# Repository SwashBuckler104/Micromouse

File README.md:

# Micromouse
80 x 80 mm Micromouse,

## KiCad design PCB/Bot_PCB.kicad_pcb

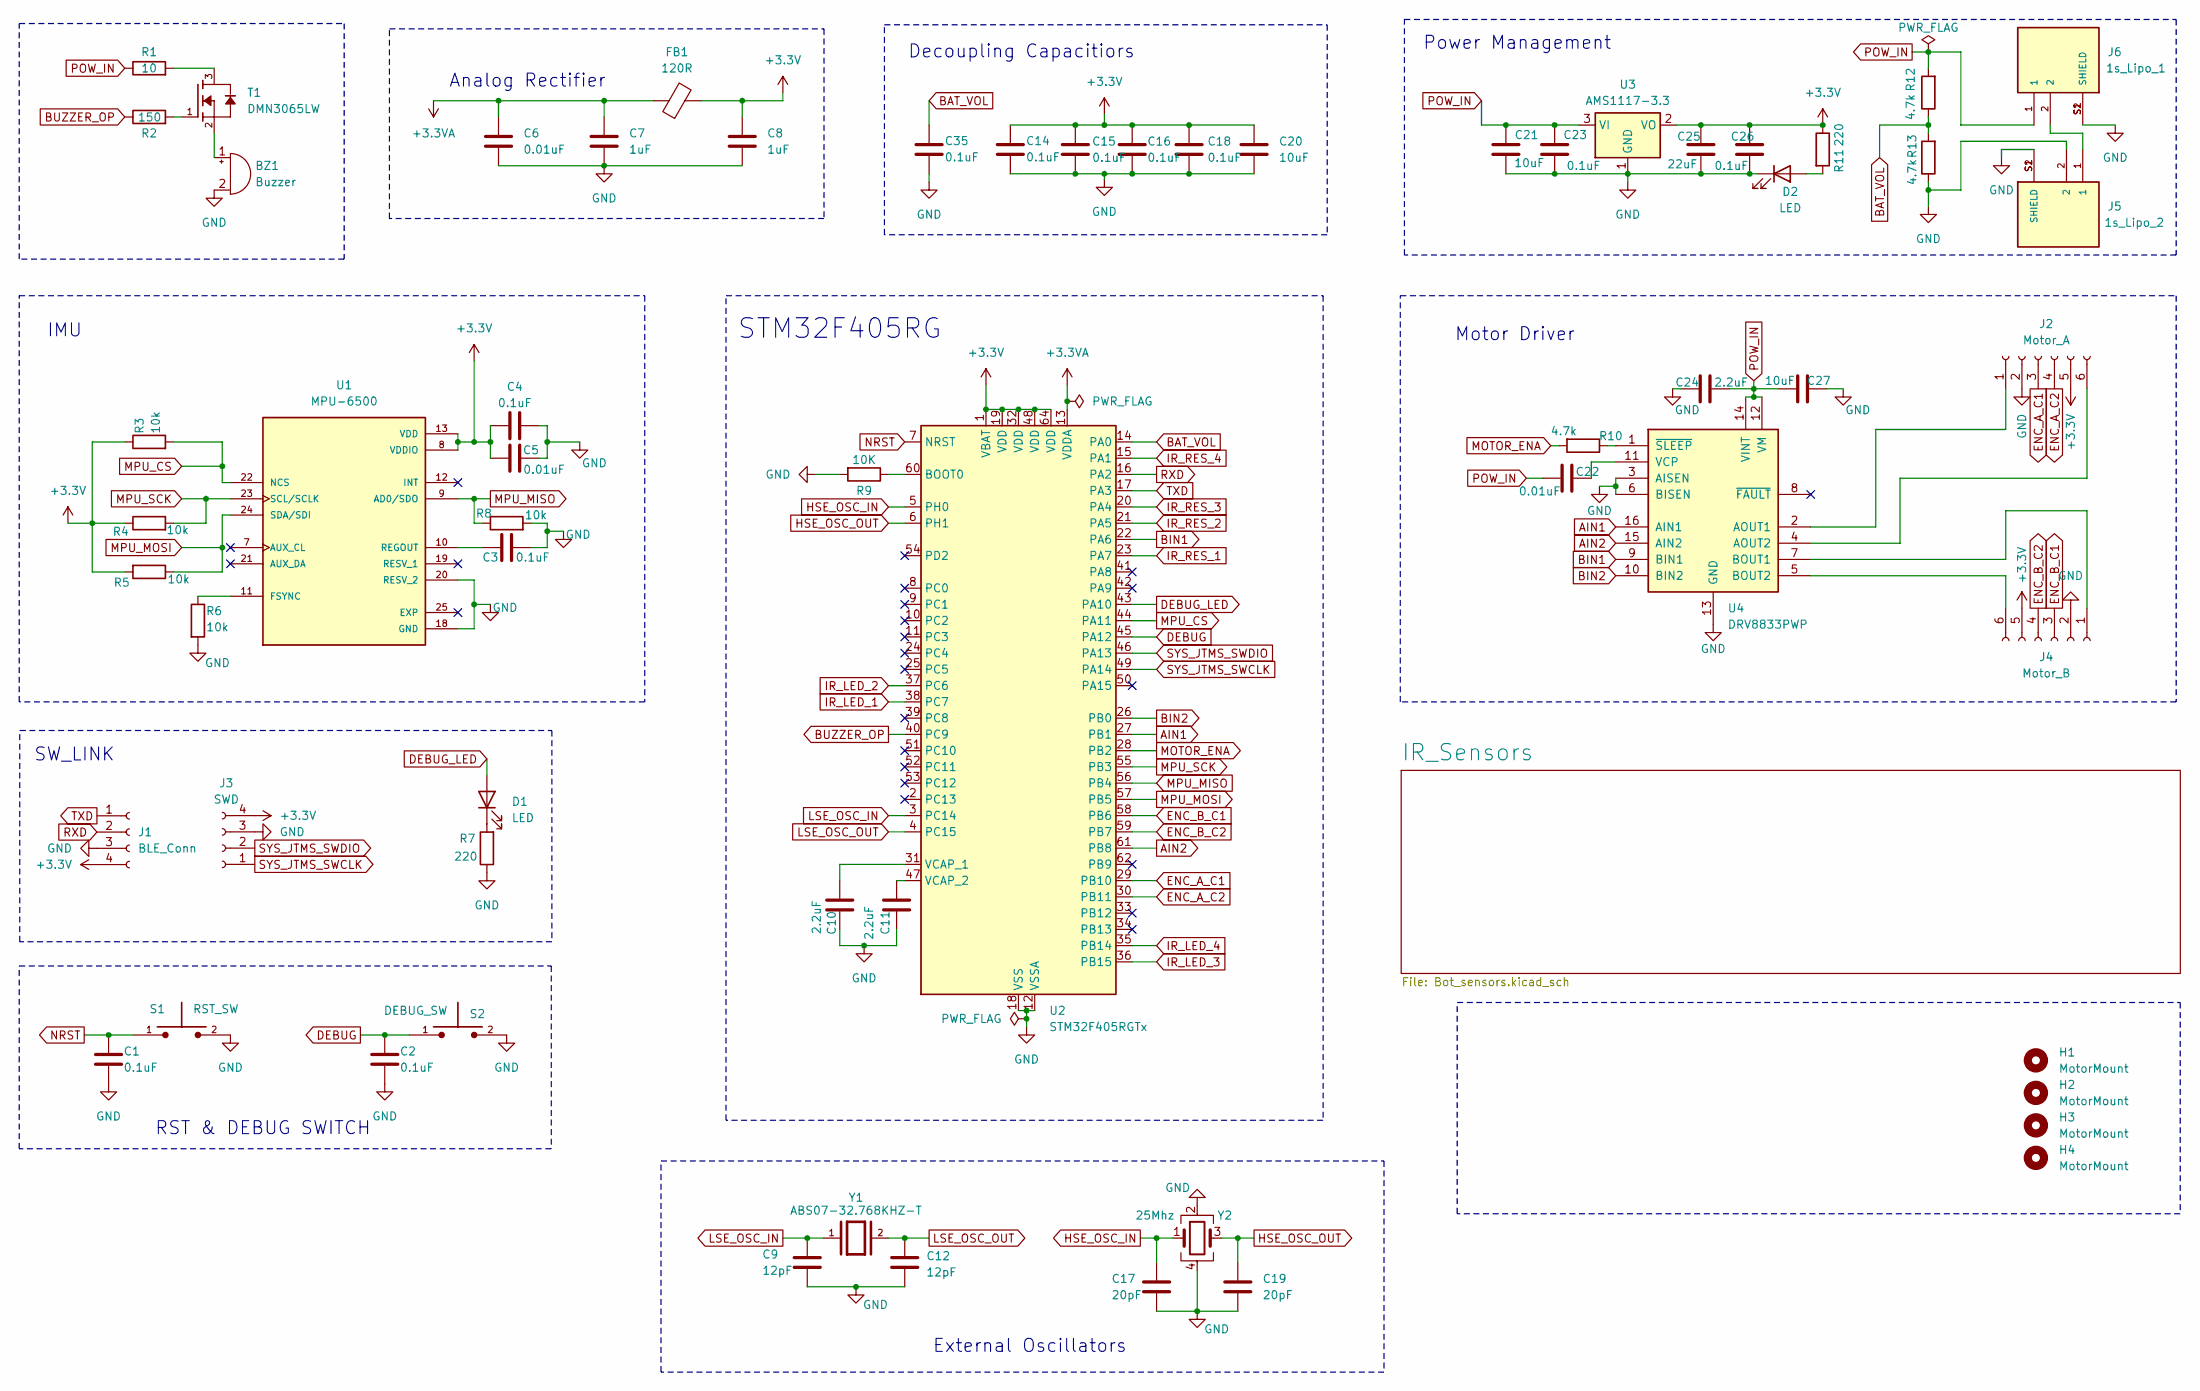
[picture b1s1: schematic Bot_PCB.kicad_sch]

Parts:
BZ1: Buzzer; Buzzer_Murata_PKMCS0909E
C1, C2, C3, C4, C14, C15, C16, C18, C23, C26, C35: 0.1uF; C_0402_1005Metric_Pad0.74x0.62mm_HandSolder
C5, C6, C22: 0.01uF; C_0402_1005Metric_Pad0.74x0.62mm_HandSolder
C7, C8: 1uF; C_0603_1608Metric_Pad1.08x0.95mm_HandSolder
C9, C12: 12pF; C_0402_1005Metric_Pad0.74x0.62mm_HandSolder
C10, C11, C24: 2.2uF; C_0603_1608Metric_Pad1.08x0.95mm_HandSolder
C17, C19: 20pF; C_0402_1005Metric_Pad0.74x0.62mm_HandSolder
C20, C21, C27: 10uF; C_0603_1608Metric_Pad1.08x0.95mm_HandSolder
C25: 22uF; C_0603_1608Metric_Pad1.08x0.95mm_HandSolder
D1, D2: LED; LED_0805_2012Metric_Pad1.15x1.40mm_HandSolder
FB1: 120R; L_0603_1608Metric_Pad1.05x0.95mm_HandSolder
H1, H2, H3, H4: MotorMount; MountingHole_2.2mm_M2
J1: BLE_Conn; PinSocket_1x04_P1.00mm_Vertical
J2: Motor_A; JST_SH_BM06B-SRSS-TB_1x06-1MP_P1.00mm_Vertical
J3: SWD; PinSocket_1x04_P1.00mm_Vertical
J4: Motor_B; JST_SH_BM06B-SRSS-TB_1x06-1MP_P1.00mm_Vertical
J5: 1s_Lipo_2; JST_BM02B-SRSS-TB_LF__SN_; PARTREV N/A
J6: 1s_Lipo_1; JST_BM02B-SRSS-TB_LF__SN_; PARTREV N/A
R1: 10; R_0603_1608Metric_Pad0.98x0.95mm_HandSolder
R2: 150; R_0603_1608Metric_Pad0.98x0.95mm_HandSolder
R3, R4, R5, R6, R8: 10k; R_0402_1005Metric_Pad0.72x0.64mm_HandSolder
R7, R11: 220; R_0603_1608Metric_Pad0.98x0.95mm_HandSolder
R9: 10K; R_0402_1005Metric_Pad0.72x0.64mm_HandSolder
R10, R12, R13: 4.7k; R_0402_1005Metric_Pad0.72x0.64mm_HandSolder
S1: RST_SW; SW_TL1015AF160QG; PARTREV F
S2: DEBUG_SW; SW_TL1015AF160QG; PARTREV F
T1: DMN3065LW; SC70-3
U1: MPU-6500; QFN40P300X300X95-25N; PARTREV 1.3
U2: STM32F405RGTx; LQFP-64_10x10mm_P0.5mm
U3: AMS1117-3.3; SOT-223-3_TabPin2
U4: DRV8833PWP; HTSSOP-16-1EP_4.4x5mm_P0.65mm_EP3.4x5mm_Mask2.46x2.31mm_The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
Y1: ABS07-32.768KHZ-T; XTAL_ABS07-32.768KHZ-T; PARTREV 08.19.15; DigiKey_Part_Number 535-9542-2-ND
Y2: 25Mhz; Crystal_SMD_3225-4Pin_3.2x2.5mm_HandSoldering

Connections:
+3.3V: C4.1, C5.1, C8.1, C14.1, C15.1, C16.1, C18.1, C20.1, C25.1, C26.1, FB1.2, J1.4, J2.5, J3.4, J4.5, R3.1, R4.1, R5.2, R11.1, U1.8 (VDDIO), U1.13 (VDD), U2.1 (VBAT), U2.19 (VDD), U2.32 (VDD), U2.48 (VDD), U2.64 (VDD), U3.2 (VO); also elsewhere on the board
+3.3VA: C6.1, C7.1, FB1.1, U2.13 (VDDA)
AIN1: U2.27 (PB1), U4.16 (AIN1)
AIN2: U2.61 (PB8), U4.15 (AIN2)
BAT_VOL: C35.1, R12.1, R13.2, U2.14 (PA0)
BIN1: U2.22 (PA6), U4.9 (BIN1)
BIN2: U2.26 (PB0), U4.10 (BIN2)
BUZZER_OP: R2.1, U2.40 (PC9)
DEBUG: C2.1, S2.1, U2.45 (PA12)
DEBUG_LED: D1.2 (A), U2.43 (PA10)
ENC_A_C1: J2.3, U2.29 (PB10); also elsewhere on the board
ENC_A_C2: J2.4, U2.30 (PB11); also elsewhere on the board
ENC_B_C1: J4.3, U2.58 (PB6); also elsewhere on the board
ENC_B_C2: J4.4, U2.59 (PB7); also elsewhere on the board
GND: BZ1.2 (-), C1.2, C2.2, C3.2, C4.2, C5.2, C6.2, C7.2, C8.2, C9.2, C10.1, C11.2, C12.2, C14.2, C15.2, C16.2, C17.2, C18.2, C19.2, C20.2, C21.2, C23.2, C24.1, C25.2, C26.2, C27.2, C35.2, D2.1 (K), J1.3, J2.2, J3.3, J4.2, J5.2, J5.S1 (SHIELD), J5.S2 (SHIELD), J6.S1 (SHIELD), J6.S2 (SHIELD), R6.2, R7.1, R8.2, R9.2, R13.1, S1.2, S2.2, U1.18 (GND), U1.20 (RESV_2), U2.12 (VSSA), U2.18 (VSS), U2.63 (VSS), U3.1 (GND), U4.3 (AISEN), U4.6 (BISEN), U4.13 (GND), U4.17 (GND), Y2.2, Y2.4; also elsewhere on the board
HSE_OSC_IN: C17.1, U2.5 (PH0), Y2.1
HSE_OSC_OUT: C19.1, U2.6 (PH1), Y2.3
IR_LED_1: U2.38 (PC7); also elsewhere on the board
IR_LED_2: U2.37 (PC6); also elsewhere on the board
IR_LED_3: U2.36 (PB15); also elsewhere on the board
IR_LED_4: U2.35 (PB14); also elsewhere on the board
IR_RES_1: U2.23 (PA7); also elsewhere on the board
IR_RES_2: U2.21 (PA5); also elsewhere on the board
IR_RES_3: U2.20 (PA4); also elsewhere on the board
IR_RES_4: U2.15 (PA1); also elsewhere on the board
LSE_OSC_IN: C9.1, U2.3 (PC14), Y1.1
LSE_OSC_OUT: C12.1, U2.4 (PC15), Y1.2
MOTOR_ENA: R10.2, U2.28 (PB2)
MPU_CS: R3.2, U1.22 (NCS), U2.44 (PA11)
MPU_MISO: R8.1, U1.9 (AD0/SDO), U2.56 (PB4)
MPU_MOSI: R5.1, U1.24 (SDA/SDI), U2.57 (PB5)
MPU_SCK: R4.2, U1.23 (SCL/SCLK), U2.55 (PB3)
NRST: C1.1, S1.1, U2.7 (NRST)
unnamed: BZ1.1 (+), T1.2
unnamed: D1.1 (K), R7.2
unnamed: D2.2 (A), R11.2
unnamed 44: J2.1, U4.2 (AOUT1); also elsewhere on the board
unnamed 45: J2.6, U4.4 (AOUT2); also elsewhere on the board
unnamed 46: J4.1, U4.7 (BOUT1); also elsewhere on the board
unnamed 47: J4.6, U4.5 (BOUT2); also elsewhere on the board
unnamed 48: J5.1, J6.2; also elsewhere on the board
unnamed: R1.2, T1.3
unnamed: R2.2, T1.1
unnamed: R6.1, U1.11 (FSYNC)
unnamed: C3.1, U1.10 (REGOUT)
unnamed: R9.1, U2.60 (BOOT0)
unnamed: C10.2, U2.31 (VCAP_1)
unnamed: C11.1, U2.47 (VCAP_2)
unnamed: C22.1, U4.11 (VCP)
unnamed: R10.1, U4.1 (~SLEEP)
POW_IN: C21.1, C22.2, C23.1, C24.2, C27.1, J6.1, R1.1, R12.2, U3.3 (VI), U4.12 (VM), U4.14 (VINT); also elsewhere on the board
RXD: J1.2, U2.16 (PA2); also elsewhere on the board
SYS_JTMS_SWCLK: J3.1, U2.49 (PA14); also elsewhere on the board
SYS_JTMS_SWDIO: J3.2, U2.46 (PA13); also elsewhere on the board
TXD: J1.1, U2.17 (PA3); also elsewhere on the board

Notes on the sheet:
RST & DEBUG SWITCH
SW_LINK
Power Management
External Oscillators
Motor Driver
STM32F405RG
IMU
Analog Rectifier
Decoupling Capacitiors

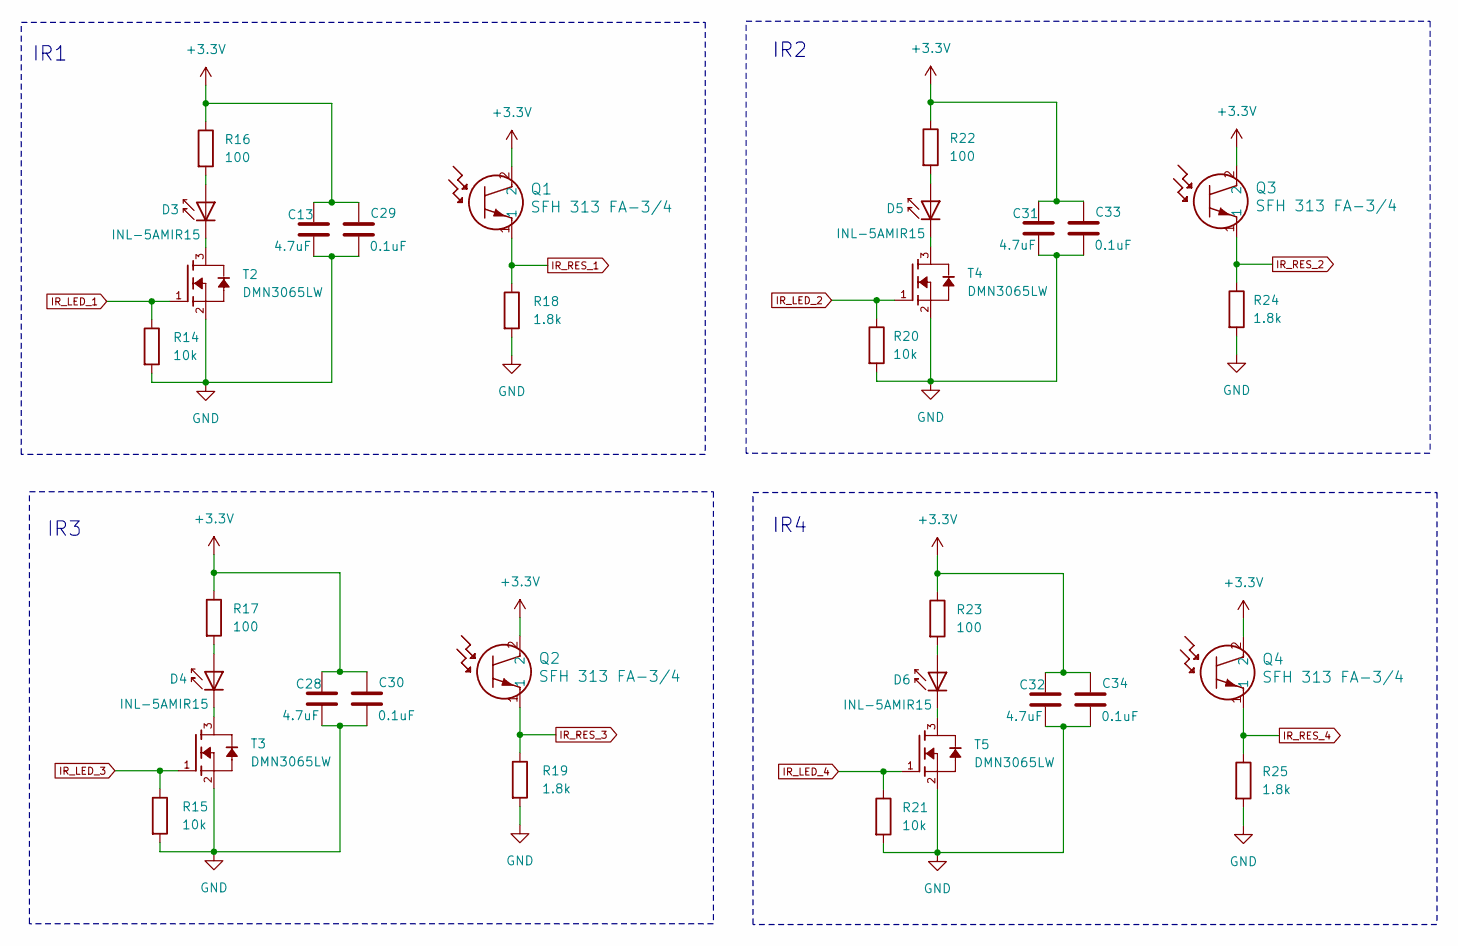
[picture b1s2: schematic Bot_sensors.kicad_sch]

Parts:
C13, C28, C31, C32: 4.7uF; C_0603_1608Metric_Pad1.08x0.95mm_HandSolder
C29, C30, C33, C34: 0.1uF; C_0402_1005Metric_Pad0.74x0.62mm_HandSolder
D3, D4, D5, D6: INL-5AMIR15; LED_D5.0mm_Horizontal_O1.27mm_Z3.0mm_Clear
Q1, Q2, Q3, Q4: SFH 313 FA-3/4; LED_D5.0mm_Horizontal_O1.27mm_Z3.0mm_IRBlack
R14, R15, R20, R21: 10k; R_0402_1005Metric_Pad0.72x0.64mm_HandSolder
R16, R17, R22, R23: 100; R_0603_1608Metric_Pad0.98x0.95mm_HandSolder
R18, R19, R24, R25: 1.8k; R_0402_1005Metric_Pad0.72x0.64mm_HandSolder
T2, T3, T4, T5: DMN3065LW; SC70-3

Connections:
+3.3V: C13.2, C28.2, C29.2, C30.2, C31.2, C32.2, C33.2, C34.2, Q1.2, Q2.2, Q3.2, Q4.2, R16.1, R17.1, R22.1, R23.1; also elsewhere on the board
GND: C13.1, C28.1, C29.1, C30.1, C31.1, C32.1, C33.1, C34.1, R14.2, R15.2, R18.2, R19.2, R20.2, R21.2, R24.2, R25.2, T2.2, T3.2, T4.2, T5.2; also elsewhere on the board
IR_LED_1: R14.1, T2.1; also elsewhere on the board
IR_LED_2: R20.1, T4.1; also elsewhere on the board
IR_LED_3: R15.1, T3.1; also elsewhere on the board
IR_LED_4: R21.1, T5.1; also elsewhere on the board
IR_RES_1: Q1.1, R18.1; also elsewhere on the board
IR_RES_2: Q3.1, R24.1; also elsewhere on the board
IR_RES_3: Q2.1, R19.1; also elsewhere on the board
IR_RES_4: Q4.1, R25.1; also elsewhere on the board
unnamed: D3.2 (A), R16.2
unnamed: D3.1 (K), T2.3
unnamed: D4.2 (A), R17.2
unnamed: D4.1 (K), T3.3
unnamed: D5.2 (A), R22.2
unnamed: D5.1 (K), T4.3
unnamed: D6.2 (A), R23.2
unnamed: D6.1 (K), T5.3

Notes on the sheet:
IR4
IR3
IR2
IR1

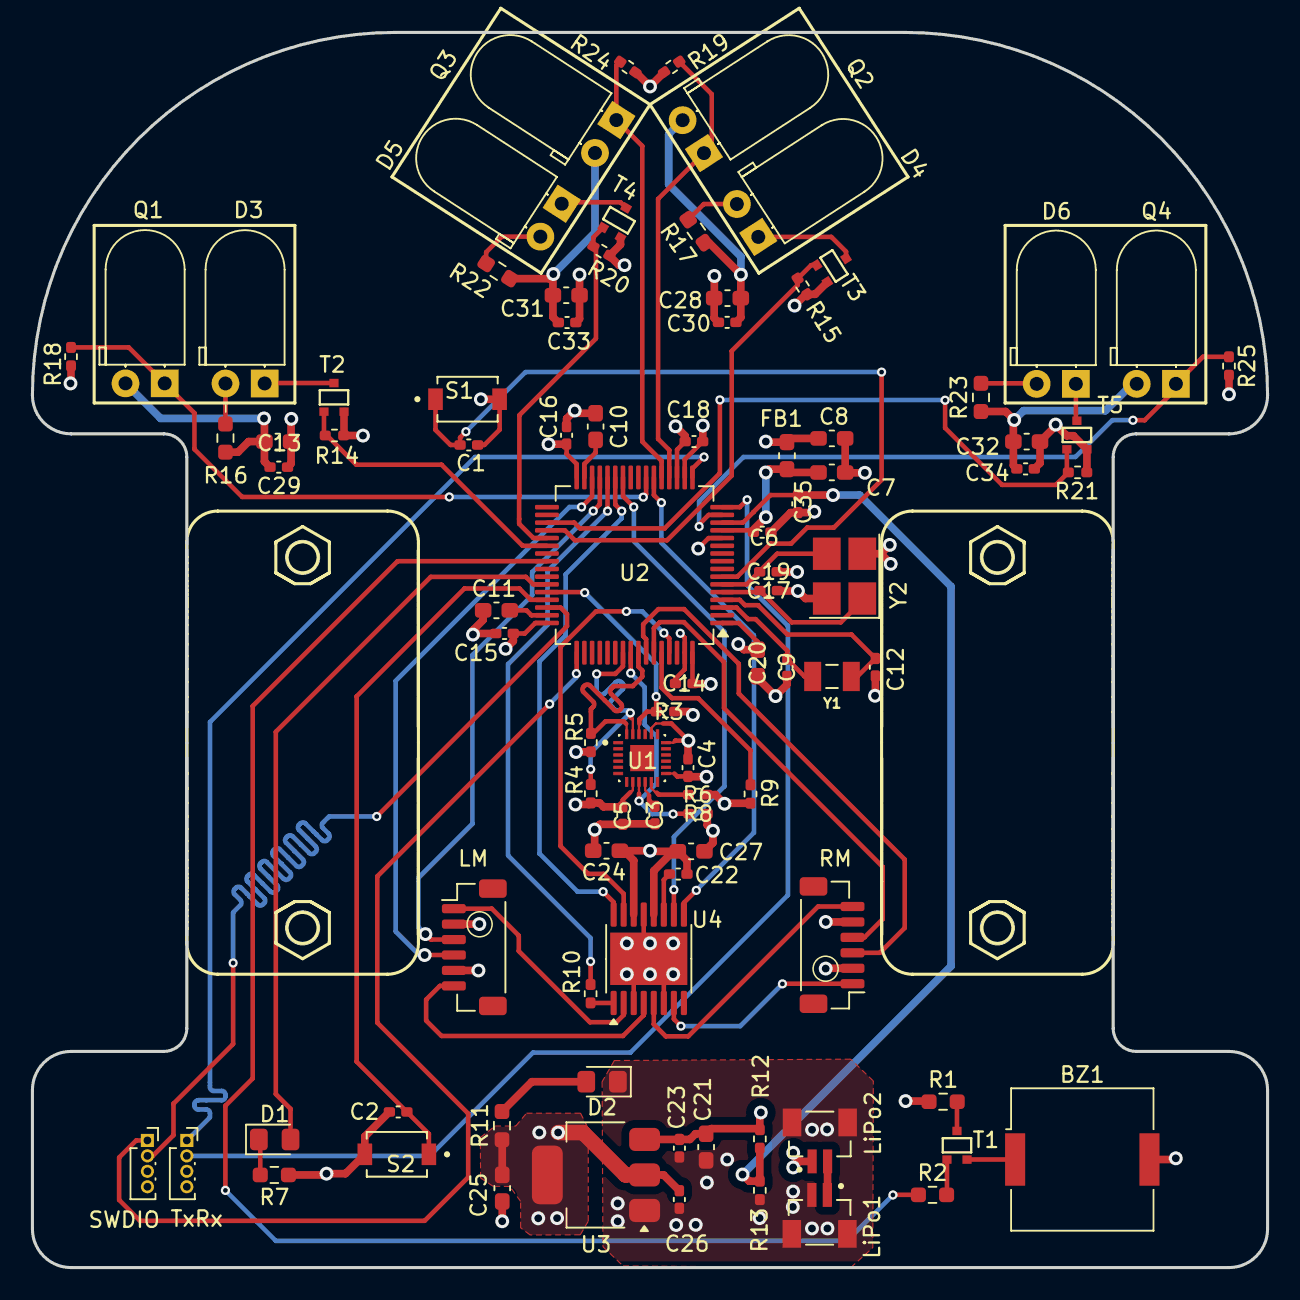
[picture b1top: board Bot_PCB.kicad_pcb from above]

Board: 4 copper layers, 80.0 x 80.0 mm, 95 parts (0 on the bottom side), 63 nets.

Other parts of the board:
LM: Motor_A; JST_SH_BM06B-SRSS-TB_1x06-1MP_P1.00mm_Vertical
LiPo1: 1s_Lipo_2; JST_BM02B-SRSS-TB_LF__SN_
LiPo2: 1s_Lipo_1; JST_BM02B-SRSS-TB_LF__SN_
RM: Motor_B; JST_SH_BM06B-SRSS-TB_1x06-1MP_P1.00mm_Vertical
SWDIO: SWD; PinSocket_1x04_P1.00mm_Vertical
TxRx: BLE_Conn; PinSocket_1x04_P1.00mm_Vertical

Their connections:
+3.3V: LM.5, RM.5, SWDIO.4, TxRx.4; also elsewhere on the board
ENC_A_C1: LM.3; also elsewhere on the board
ENC_A_C2: LM.4; also elsewhere on the board
ENC_B_C1: RM.3; also elsewhere on the board
ENC_B_C2: RM.4; also elsewhere on the board
GND: LM.2, LiPo1.2, LiPo1.S1 (SHIELD), LiPo1.S2 (SHIELD), LiPo2.S1 (SHIELD), LiPo2.S2 (SHIELD), RM.2, SWDIO.3, TxRx.3; also elsewhere on the board
unnamed 44: LM.1; also elsewhere on the board
unnamed 45: LM.6; also elsewhere on the board
unnamed 46: RM.1; also elsewhere on the board
unnamed 47: RM.6; also elsewhere on the board
unnamed 48: LiPo1.1, LiPo2.2; also elsewhere on the board
POW_IN: LiPo2.1; also elsewhere on the board
RXD: TxRx.2; also elsewhere on the board
SYS_JTMS_SWCLK: SWDIO.1; also elsewhere on the board
SYS_JTMS_SWDIO: SWDIO.2; also elsewhere on the board
TXD: TxRx.1; also elsewhere on the board

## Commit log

2024-10-04 Created 3D_Model Folder
2024-10-04 Udated_3DModel
2024-10-04 Created PCB Folder
2024-10-04 Create ABS07-32.768KHZ-T
2024-10-04 Rename .gitkeep to Instructions
2024-10-04 Updated ABS07
2024-10-04 Create BM02B-SRSS-TB_LF__SN
2024-10-04 Create Instructions
2024-10-04 Create Ins
2024-10-04 Create Tips
2024-10-04 Uploaded Pictures
